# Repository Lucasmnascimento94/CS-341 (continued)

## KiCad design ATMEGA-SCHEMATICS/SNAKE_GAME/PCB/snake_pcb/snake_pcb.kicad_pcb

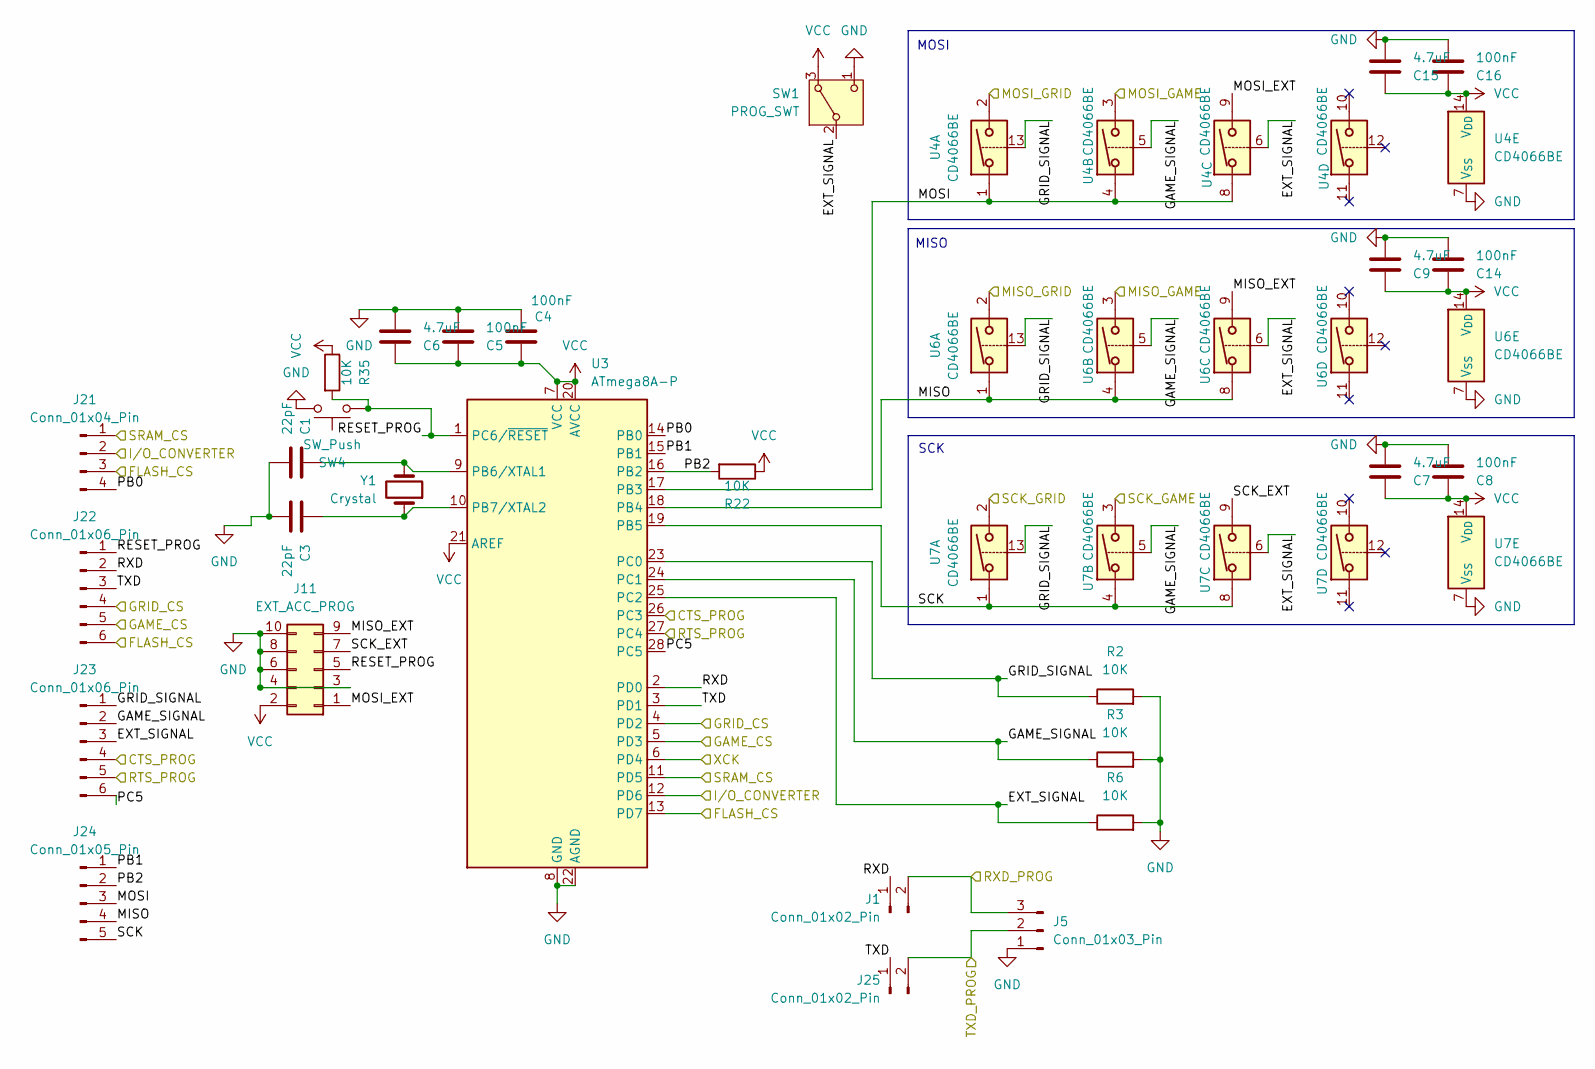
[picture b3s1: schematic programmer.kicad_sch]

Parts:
C1, C3: 22pF; CP_Radial_D5.0mm_P2.50mm
C4, C5, C8, C14, C16: 100nF; C_Disc_D7.5mm_W5.0mm_P5.00mm
C6, C7, C9, C15: 4.7uF; C_Disc_D7.5mm_W5.0mm_P5.00mm
J1: Conn_01x02_Pin; PinSocket_1x02_P2.54mm_Vertical
J5: Conn_01x03_Pin; PinSocket_1x03_P2.54mm_Vertical
J11: EXT_ACC_PROG; IDC-Header_2x05_P2.54mm_Vertical
J21: Conn_01x04_Pin; PinHeader_1x04_P2.54mm_Vertical
J22, J23: Conn_01x06_Pin; PinHeader_1x06_P2.54mm_Vertical
J24: Conn_01x05_Pin; PinHeader_1x05_P2.54mm_Vertical
J25: Conn_01x02_Pin; PinHeader_1x02_P2.54mm_Vertical
R2, R3, R6, R22, R35: 10K; R_Axial_DIN0207_L6.3mm_D2.5mm_P10.16mm_Horizontal
SW1: PROG_SWT; SW_Slide_SPDT_Straight_CK_OS102011MS2Q
SW4: SW_Push; SW_PUSH_1P1T_6x3.5mm_H4.3_APEM_MJTP1243
U3: ATmega8A-P; DIP-28_W7.62mm
U4, U6, U7: CD4066BE; DIP-14_W7.62mm
Y1: Crystal; Resonator-2Pin_W6.0mm_H3.0mm

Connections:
/converter/CTS_CONV: J23.4, U3.26 (PC3); also elsewhere on the board
/converter/RTS_CONV: J23.5, U3.27 (PC4); also elsewhere on the board
/converter/RXD_CONV: J5.2, J25.2; also elsewhere on the board
/converter/TXD_CONV: J1.2, J5.3; also elsewhere on the board
/converter/WAKE_UP: J21.2, U3.12 (PD6); also elsewhere on the board
/game/MISO_GAME: U6.3; also elsewhere on the board
/game/MOSI_GAME: U4.3; also elsewhere on the board
/game/RESET_GAME: J22.5, U3.5 (PD3); also elsewhere on the board
/game/SCK_GAME: U7.3; also elsewhere on the board
/grid/MISO_GRID: U6.2; also elsewhere on the board
/grid/MOSI_GRID: U4.2; also elsewhere on the board
/grid/RESET_GRID: J22.4, U3.4 (PD2); also elsewhere on the board
/grid/SCK_GRID: U7.2; also elsewhere on the board
/grid/SRAM_CS: J21.1, U3.11 (PD5); also elsewhere on the board
/programmer/EXT_SIGNAL: J23.3, R6.1, SW1.2 (B), U3.25 (PC2), U4.6, U6.6, U7.6
/programmer/GAME_SIGNAL: J23.2, R3.1, U3.24 (PC1), U4.5, U6.5, U7.5
/programmer/GRID_SIGNAL: J23.1, R2.1, U3.23 (PC0), U4.13, U6.13, U7.13
/programmer/MISO: J24.4, U3.18 (PB4), U6.1, U6.4, U6.8
/programmer/MISO_EXT: J11.9, U6.9
/programmer/MOSI: J24.3, U3.17 (PB3), U4.1, U4.4, U4.8
/programmer/MOSI_EXT: J11.1, U4.9
/programmer/PB0: J21.4, U3.14 (PB0)
/programmer/PB1: J24.1, U3.15 (PB1)
/programmer/PB2: J24.2, R22.2, U3.16 (PB2)
/programmer/PC5: J23.6, U3.28 (PC5)
/programmer/RESET_PROG: J11.5, J22.1, R35.2, SW4.1, U3.1 (PC6/~RESET)
/programmer/RXD: J1.1, J22.2, U3.2 (PD0)
/programmer/SCK: J24.5, U3.19 (PB5), U7.1, U7.4, U7.8
/programmer/SCK_EXT: J11.7, U7.9
/programmer/TXD: J22.3, J25.1, U3.3 (PD1)
GND: C1.2, C3.2, C4.2, C5.2, C6.2, C7.2, C8.2, C9.2, C14.2, C15.2, C16.2, J5.1, J11.3, J11.4, J11.6, J11.8, J11.10, R2.2, R3.2, R6.2, SW1.1 (C), SW4.2, U3.8 (GND), U3.22 (AGND), U4.7 (V_{SS}), U6.7 (V_{SS}), U7.7 (V_{SS}); also elsewhere on the board
unnamed: C1.1, U3.9 (PB6/XTAL1), Y1.2
unnamed: C3.1, U3.10 (PB7/XTAL2), Y1.1
VCC: C4.1, C5.1, C6.1, C7.1, C8.1, C9.1, C14.1, C15.1, C16.1, J11.2, R22.1, R35.1, SW1.3 (A), U3.7 (VCC), U3.20 (AVCC), U3.21 (AREF), U4.14 (V_{DD}), U6.14 (V_{DD}), U7.14 (V_{DD}); also elsewhere on the board

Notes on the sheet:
SCK
MISO
MOSI

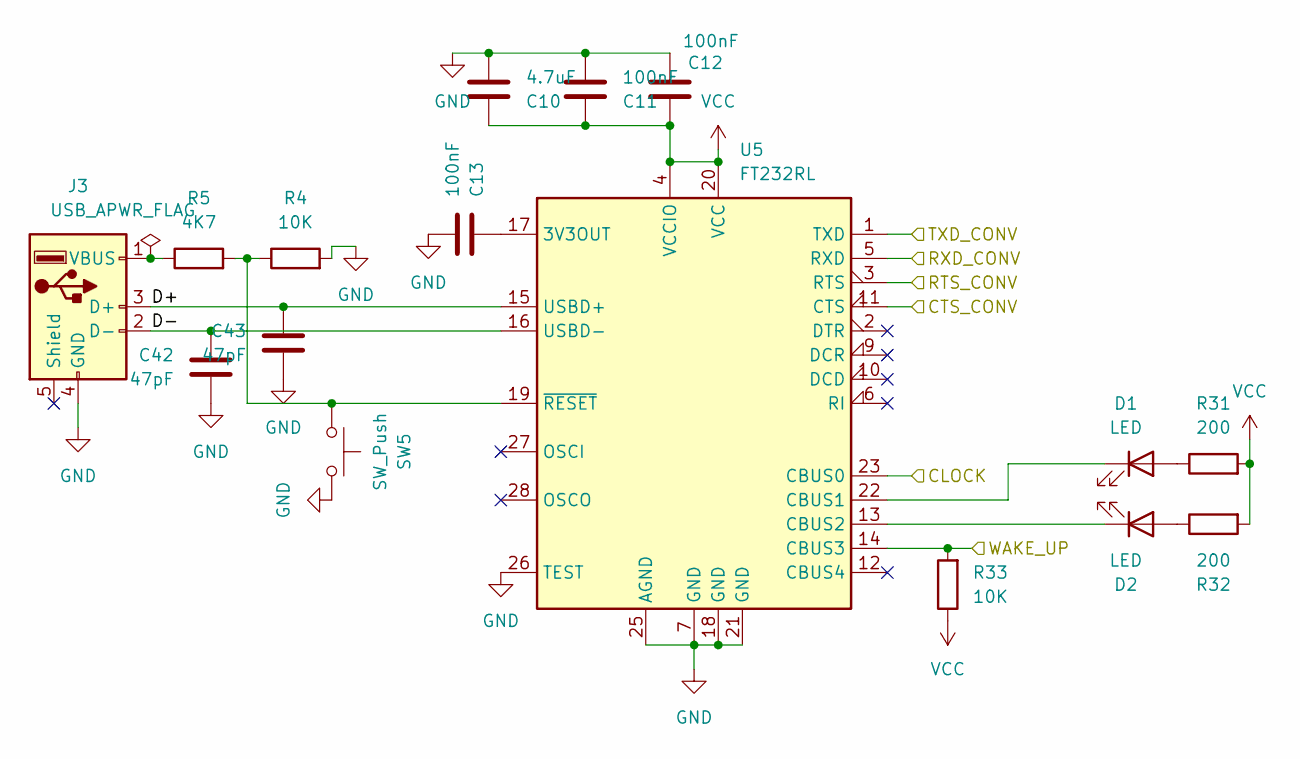
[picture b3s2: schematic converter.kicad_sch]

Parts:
C10: 4.7uF; C_Disc_D7.5mm_W5.0mm_P5.00mm
C11, C12, C13: 100nF; C_Disc_D7.5mm_W5.0mm_P5.00mm
C42, C43: 47pF; C_Disc_D7.5mm_W5.0mm_P5.00mm
D1, D2: LED; LED_D1.8mm_W3.3mm_H2.4mm
J3: USB_A; USB_B_Lumberg_2411_02_Horizontal
R4, R33: 10K; R_Axial_DIN0207_L6.3mm_D2.5mm_P10.16mm_Horizontal
R5: 4K7; R_Axial_DIN0207_L6.3mm_D2.5mm_P10.16mm_Horizontal
R31, R32: 200; R_Axial_DIN0207_L6.3mm_D2.5mm_P10.16mm_Horizontal
SW5: SW_Push; SW_PUSH_1P1T_6x3.5mm_H4.3_APEM_MJTP1243
U5: FT232RL; DIP-28_W15.24mm_LongPads

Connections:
/converter/CTS_CONV: U5.11 (CTS); also elsewhere on the board
/converter/D+: C43.1, J3.3 (D+), U5.15 (USBD+)
/converter/D-: C42.1, J3.2 (D-), U5.16 (USBD-)
/converter/RTS_CONV: U5.3 (RTS); also elsewhere on the board
/converter/RXD_CONV: U5.5 (RXD); also elsewhere on the board
/converter/TXD_CONV: U5.1 (TXD); also elsewhere on the board
/converter/WAKE_UP: R33.2, U5.14 (CBUS3); also elsewhere on the board
GND: C10.2, C11.2, C12.2, C13.2, C42.2, C43.2, J3.4 (GND), R4.2, SW5.2, U5.7 (GND), U5.18 (GND), U5.21 (GND), U5.25 (AGND), U5.26 (TEST); also elsewhere on the board
unnamed: D1.2 (A), R31.1
unnamed: D1.1 (K), U5.22 (CBUS1)
unnamed: D2.2 (A), R32.1
unnamed: D2.1 (K), U5.13 (CBUS2)
unnamed: J3.1 (VBUS), R5.1
unnamed: C13.1, U5.17 (3V3OUT)
unnamed: R4.1, R5.2, SW5.1, U5.19 (~RESET)
VCC: C10.1, C11.1, C12.1, R31.2, R32.2, R33.1, U5.4 (VCCIO), U5.20 (VCC); also elsewhere on the board

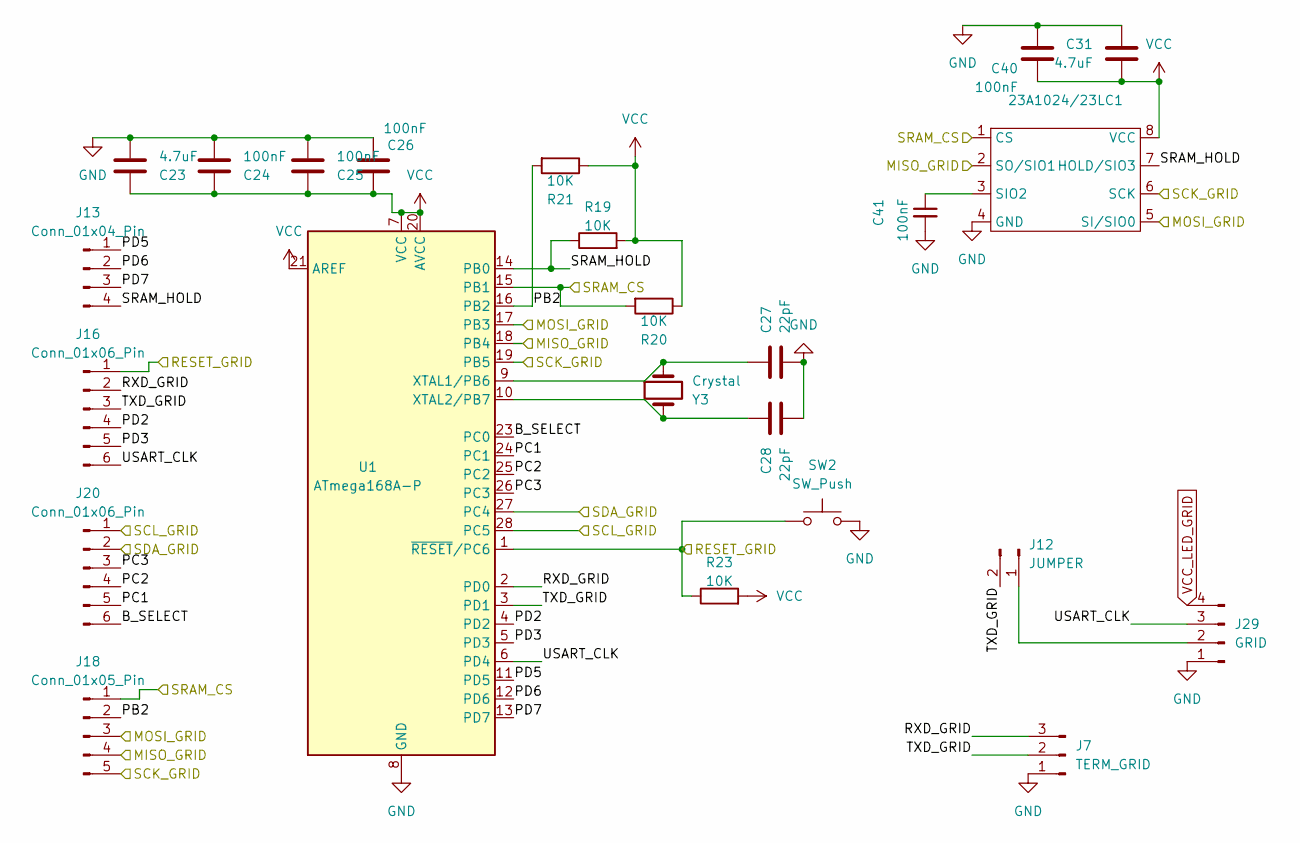
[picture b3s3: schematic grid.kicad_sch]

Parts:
23A1024/23LC1: CERDIP-8_W7.62mm_SideBrazed_Socket
C23, C31: 4.7uF; C_Disc_D7.5mm_W5.0mm_P5.00mm
C24, C25, C26, C40, C41: 100nF; C_Disc_D7.5mm_W5.0mm_P5.00mm
C27, C28: 22pF; CP_Radial_D5.0mm_P2.50mm
J7: TERM_GRID; PinSocket_1x03_P2.54mm_Vertical
J12: JUMPER; PinHeader_1x02_P2.54mm_Vertical
J13: Conn_01x04_Pin; PinHeader_1x04_P2.54mm_Vertical
J16, J20: Conn_01x06_Pin; PinHeader_1x06_P2.54mm_Vertical
J18: Conn_01x05_Pin; PinHeader_1x05_P2.54mm_Vertical
J29: GRID; PinHeader_1x04_P2.54mm_Vertical
R19, R20, R21, R23: 10K; R_Axial_DIN0207_L6.3mm_D2.5mm_P10.16mm_Horizontal
SW2: SW_Push; SW_PUSH_1P1T_6x3.5mm_H4.3_APEM_MJTP1243
U1: ATmega168A-P; DIP-28_W7.62mm
Y3: Crystal; Resonator-2Pin_W6.0mm_H3.0mm

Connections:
/game/SCL_GAME: J20.1, U1.28 (PC5); also elsewhere on the board
/game/SDA_GAME: J20.2, U1.27 (PC4); also elsewhere on the board
/grid/B_SELECT: J20.6, U1.23 (PC0)
/grid/MISO_GRID: 23A1024/23LC1.2 (SO/SIO1), J18.4, U1.18 (PB4); also elsewhere on the board
/grid/MOSI_GRID: 23A1024/23LC1.5 (SI/SIO0), J18.3, U1.17 (PB3); also elsewhere on the board
/grid/PB2: J18.2, R21.2, U1.16 (PB2)
/grid/PC2: J20.4, U1.25 (PC2)
/grid/PC3: J20.3, U1.26 (PC3)
/grid/PD2: J16.4, U1.4 (PD2)
/grid/PD3: J16.5, U1.5 (PD3)
/grid/PD5: J13.1, U1.11 (PD5)
/grid/PD6: J13.2, U1.12 (PD6)
/grid/PD7: J13.3, U1.13 (PD7)
/grid/RESET_GRID: J16.1, R23.1, SW2.1, U1.1 (~RESET/PC6); also elsewhere on the board
/grid/RXD_GRID: J7.3, J16.2, U1.2 (PD0)
/grid/SCK_GRID: 23A1024/23LC1.6 (SCK), J18.5, U1.19 (PB5); also elsewhere on the board
/grid/SRAM_CS: 23A1024/23LC1.1 (CS), J18.1, R20.2, U1.15 (PB1); also elsewhere on the board
/grid/SRAM_HOLD: 23A1024/23LC1.7 (HOLD/SIO3), J13.4, R19.1, U1.14 (PB0)
/grid/TXD_GRID: J7.2, J12.2, J16.3, U1.3 (PD1)
/grid/USART_CLK: J16.6, J29.3, U1.6 (PD4)
GND: 23A1024/23LC1.4 (GND), C23.2, C24.2, C25.2, C26.2, C27.2, C28.2, C31.1, C40.1, C41.2, J7.1, J29.1, SW2.2, U1.8 (GND), U1.22 (GND); also elsewhere on the board
unnamed: 23A1024/23LC1.3 (SIO2), C41.1
unnamed: J12.1, J29.2
unnamed: C27.1, U1.9 (XTAL1/PB6), Y3.1
unnamed: C28.1, U1.10 (XTAL2/PB7), Y3.2
REG_EN_LOW: J20.5, U1.24 (PC1); also elsewhere on the board
VCC: 23A1024/23LC1.8 (VCC), C23.1, C24.1, C25.1, C26.1, C31.2, C40.2, R19.2, R20.1, R21.1, R23.2, U1.7 (VCC), U1.20 (AVCC), U1.21 (AREF); also elsewhere on the board
VCC_LED_GRID: J29.4; also elsewhere on the board

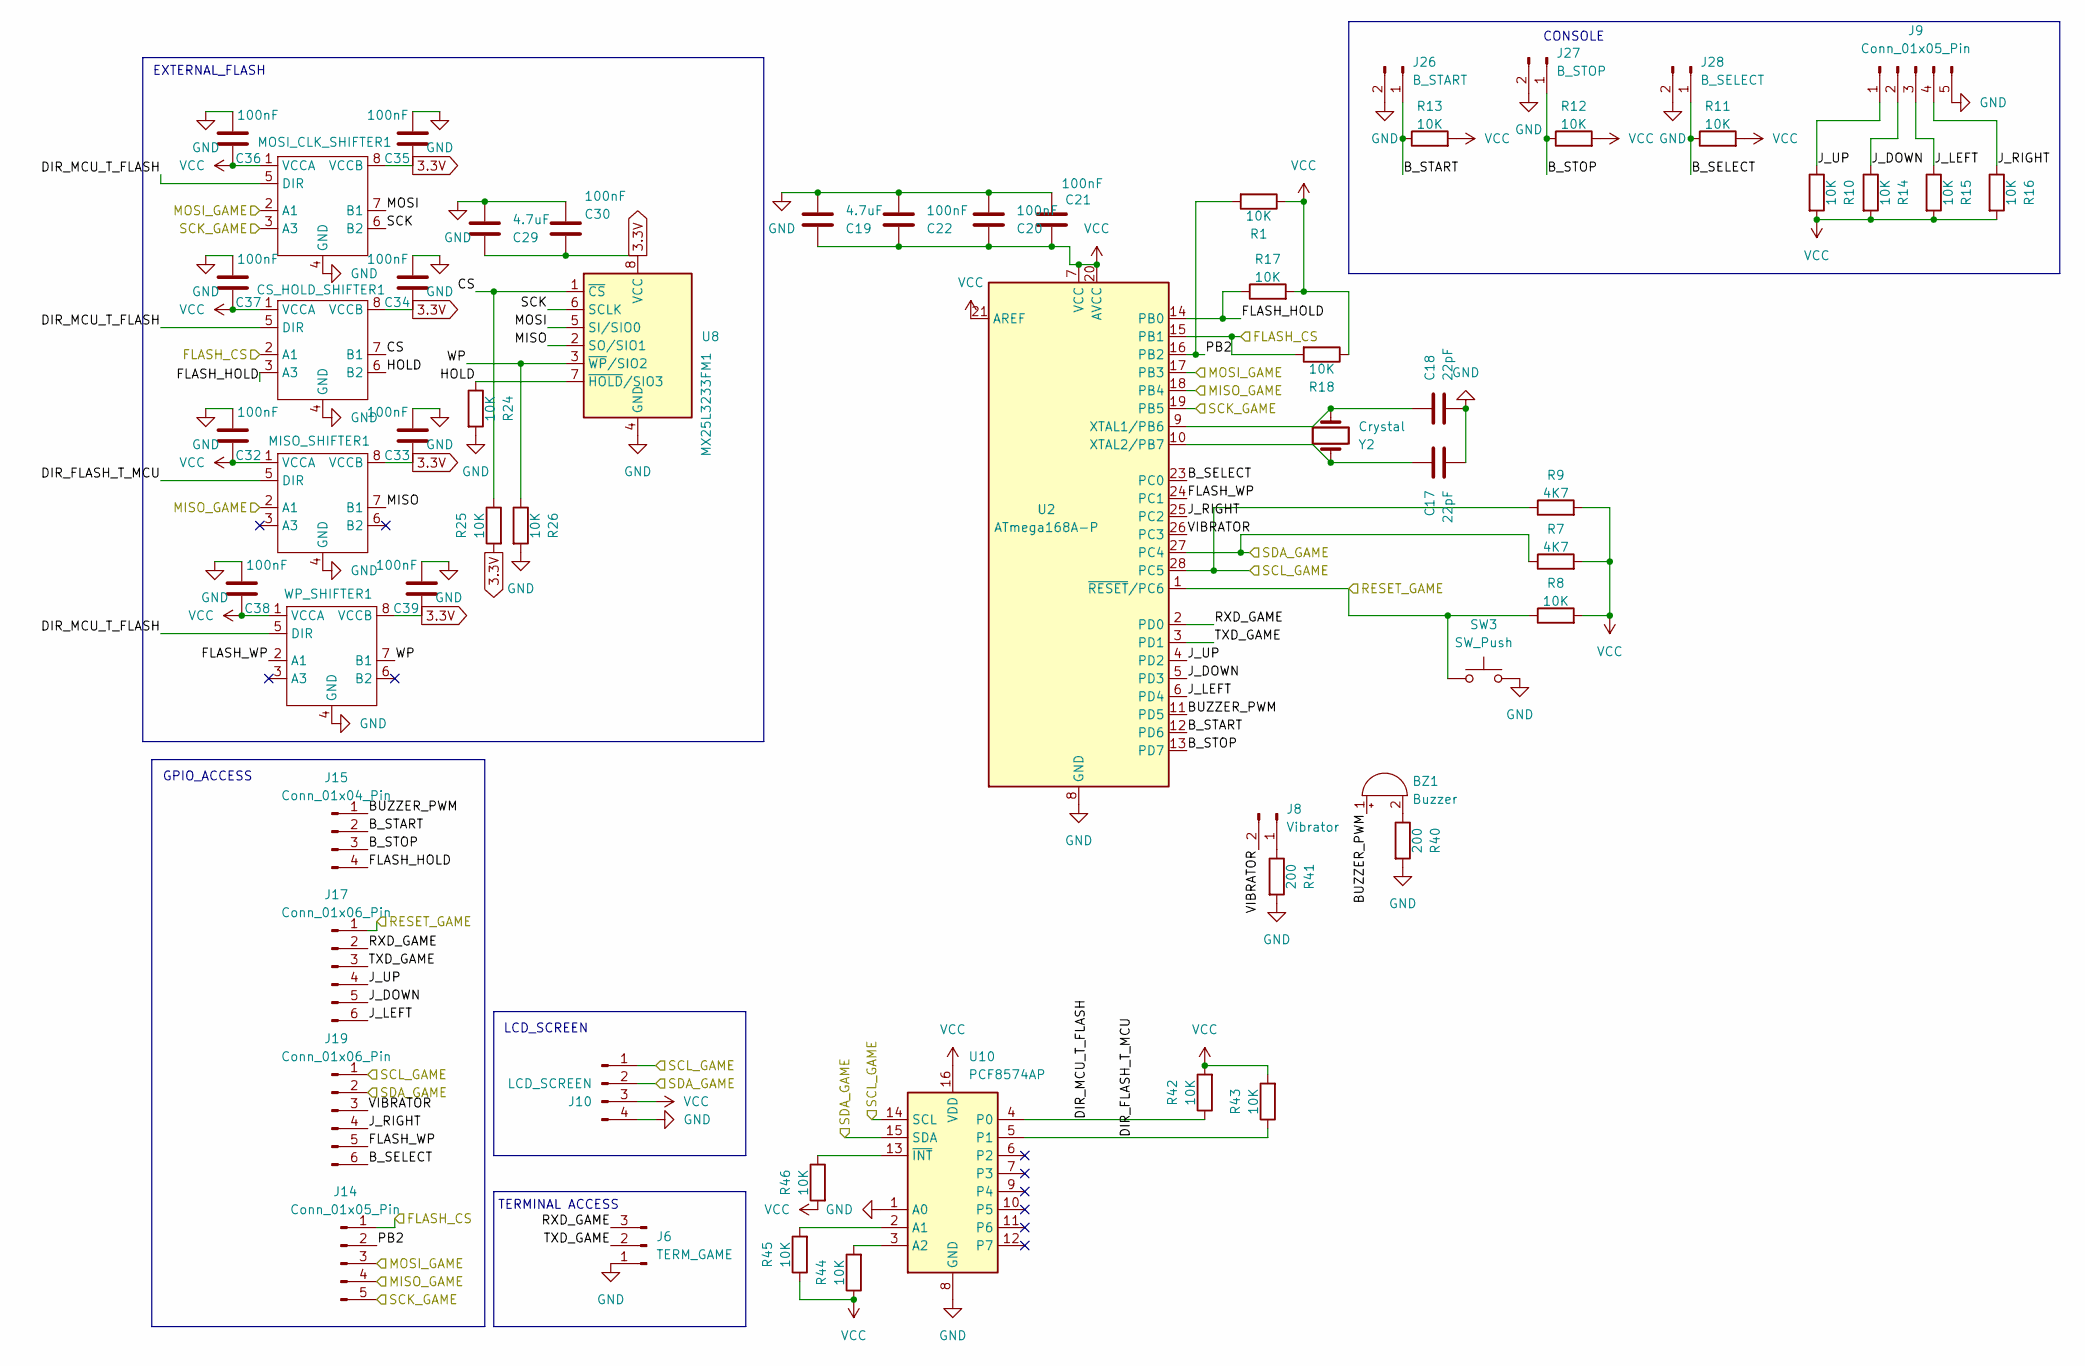
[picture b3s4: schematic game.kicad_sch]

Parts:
BZ1: Buzzer; Buzzer_12x9.5RM7.6
C17, C18: 22pF; CP_Radial_D5.0mm_P2.50mm
C19, C29: 4.7uF; C_Disc_D7.5mm_W5.0mm_P5.00mm
C20, C21, C22, C30, C32, C33, C34, C35, C36, C37, C38, C39: 100nF; C_Disc_D7.5mm_W5.0mm_P5.00mm
CS_HOLD_SHIFTER1: DIP-8_W7.62mm
J6: TERM_GAME; PinSocket_1x03_P2.54mm_Vertical
J8: Vibrator; PinHeader_1x02_P2.54mm_Vertical
J9: Conn_01x05_Pin; PinSocket_1x05_P2.54mm_Vertical
J10: LCD_SCREEN; PinSocket_1x04_P2.54mm_Vertical
J14: Conn_01x05_Pin; PinHeader_1x05_P2.54mm_Vertical
J15: Conn_01x04_Pin; PinHeader_1x04_P2.54mm_Vertical
J17, J19: Conn_01x06_Pin; PinHeader_1x06_P2.54mm_Vertical
J26: B_START; PinHeader_1x02_P2.54mm_Vertical
J27: B_STOP; PinHeader_1x02_P2.54mm_Vertical
J28: B_SELECT; PinHeader_1x02_P2.54mm_Vertical
MISO_SHIFTER1: DIP-8_W7.62mm
MOSI_CLK_SHIFTER1: DIP-8_W7.62mm
R1, R8, R10, R11, R12, R13, R14, R15, R16, R17, R18, R24, R25, R26, R42, R43, R44, R45, R46: 10K; R_Axial_DIN0207_L6.3mm_D2.5mm_P10.16mm_Horizontal
R7, R9: 4K7; R_Axial_DIN0207_L6.3mm_D2.5mm_P10.16mm_Horizontal
R40, R41: 200; R_Axial_DIN0207_L6.3mm_D2.5mm_P10.16mm_Horizontal
SW3: SW_Push; SW_PUSH_1P1T_6x3.5mm_H4.3_APEM_MJTP1243
U2: ATmega168A-P; DIP-28_W7.62mm
U8: MX25L3233FM1; CERDIP-8_W7.62mm_SideBrazed_Socket
U10: PCF8574AP; DIP-16_W7.62mm
WP_SHIFTER1: DIP-8_W7.62mm
Y2: Crystal; Resonator-2Pin_W6.0mm_H3.0mm

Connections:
3.3V: C29.1, C30.1, C33.1, C34.1, C35.1, C39.1, CS_HOLD_SHIFTER1.8 (VCCB), MISO_SHIFTER1.8 (VCCB), MOSI_CLK_SHIFTER1.8 (VCCB), R25.2, U8.8 (VCC), WP_SHIFTER1.8 (VCCB); also elsewhere on the board
/game/BUZZER_PWM: BZ1.1 (+), J15.1, U2.11 (PD5)
/game/B_SELECT: J19.6, J28.1, R11.1, U2.23 (PC0)
/game/B_START: J15.2, J26.1, R13.1, U2.12 (PD6)
/game/B_STOP: J15.3, J27.1, R12.1, U2.13 (PD7)
/game/CS: CS_HOLD_SHIFTER1.7 (B1), R25.1, U8.1 (~CS)
/game/DIR_FLASH_T_MCU: MISO_SHIFTER1.5 (DIR), R43.1, U10.5 (P1)
/game/DIR_MCU_T_FLASH: CS_HOLD_SHIFTER1.5 (DIR), MOSI_CLK_SHIFTER1.5 (DIR), R42.1, U10.4 (P0), WP_SHIFTER1.5 (DIR)
/game/FLASH_HOLD: CS_HOLD_SHIFTER1.3 (A3), J15.4, R17.1, U2.14 (PB0)
/game/FLASH_WP: J19.5, U2.24 (PC1), WP_SHIFTER1.2 (A1)
/game/HOLD: CS_HOLD_SHIFTER1.6 (B2), R24.1, U8.7 (~HOLD/SIO3)
/game/J_DOWN: J9.2, J17.5, R14.1, U2.5 (PD3)
/game/J_LEFT: J9.3, J17.6, R15.1, U2.6 (PD4)
/game/J_RIGHT: J9.4, J19.4, R16.1, U2.25 (PC2)
/game/J_UP: J9.1, J17.4, R10.1, U2.4 (PD2)
/game/MISO: MISO_SHIFTER1.7 (B1), U8.2 (SO/SIO1)
/game/MISO_GAME: J14.4, MISO_SHIFTER1.2 (A1), U2.18 (PB4); also elsewhere on the board
/game/MOSI: MOSI_CLK_SHIFTER1.7 (B1), U8.5 (SI/SIO0)
/game/MOSI_GAME: J14.3, MOSI_CLK_SHIFTER1.2 (A1), U2.17 (PB3); also elsewhere on the board
/game/PB2: J14.2, R1.2, U2.16 (PB2)
/game/RESET_GAME: J17.1, R8.1, SW3.1, U2.1 (~RESET/PC6); also elsewhere on the board
/game/RXD_GAME: J6.3, J17.2, U2.2 (PD0)
/game/SCK: MOSI_CLK_SHIFTER1.6 (B2), U8.6 (SCLK)
/game/SCK_GAME: J14.5, MOSI_CLK_SHIFTER1.3 (A3), U2.19 (PB5); also elsewhere on the board
/game/SCL_GAME: J10.1, J19.1, R9.1, U2.28 (PC5), U10.14 (SCL); also elsewhere on the board
/game/SDA_GAME: J10.2, J19.2, R7.1, U2.27 (PC4), U10.15 (SDA); also elsewhere on the board
/game/TXD_GAME: J6.2, J17.3, U2.3 (PD1)
/game/VIBRATOR: J8.2, J19.3, U2.26 (PC3)
/game/WP: R26.1, U8.3 (~WP/SIO2), WP_SHIFTER1.7 (B1)
GND: C17.2, C18.2, C19.2, C20.2, C21.2, C22.2, C29.2, C30.2, C32.2, C33.2, C34.2, C35.2, C36.2, C37.2, C38.2, C39.2, CS_HOLD_SHIFTER1.4 (GND), J6.1, J9.5, J10.4, J26.2, J27.2, J28.2, MISO_SHIFTER1.4 (GND), MOSI_CLK_SHIFTER1.4 (GND), R24.2, R26.2, R40.2, R41.2, SW3.2, U2.8 (GND), U2.22 (GND), U8.4 (GND), U10.1 (A0), U10.8 (GND), WP_SHIFTER1.4 (GND); also elsewhere on the board
unnamed: BZ1.2 (-), R40.1
unnamed: J8.1, R41.1
unnamed: C18.1, U2.9 (XTAL1/PB6), Y2.1
unnamed: C17.1, U2.10 (XTAL2/PB7), Y2.2
unnamed: R45.2, U10.2 (A1)
unnamed: R44.2, U10.3 (A2)
unnamed: R46.1, U10.13 (~INT)
VCC: C19.1, C20.1, C21.1, C22.1, C32.1, C36.1, C37.1, C38.1, CS_HOLD_SHIFTER1.1 (VCCA), J10.3, MISO_SHIFTER1.1 (VCCA), MOSI_CLK_SHIFTER1.1 (VCCA), R1.1, R7.2, R8.2, R9.2, R10.2, R11.2, R12.2, R13.2, R14.2, R15.2, R16.2, R17.2, R18.1, R42.2, R43.2, R44.1, R45.1, R46.2, U2.7 (VCC), U2.20 (AVCC), U2.21 (AREF), U10.16 (VDD), WP_SHIFTER1.1 (VCCA); also elsewhere on the board

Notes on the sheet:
TERMINAL ACCESS
GPIO_ACCESS
CONSOLE
EXTERNAL_FLASH
LCD_SCREEN

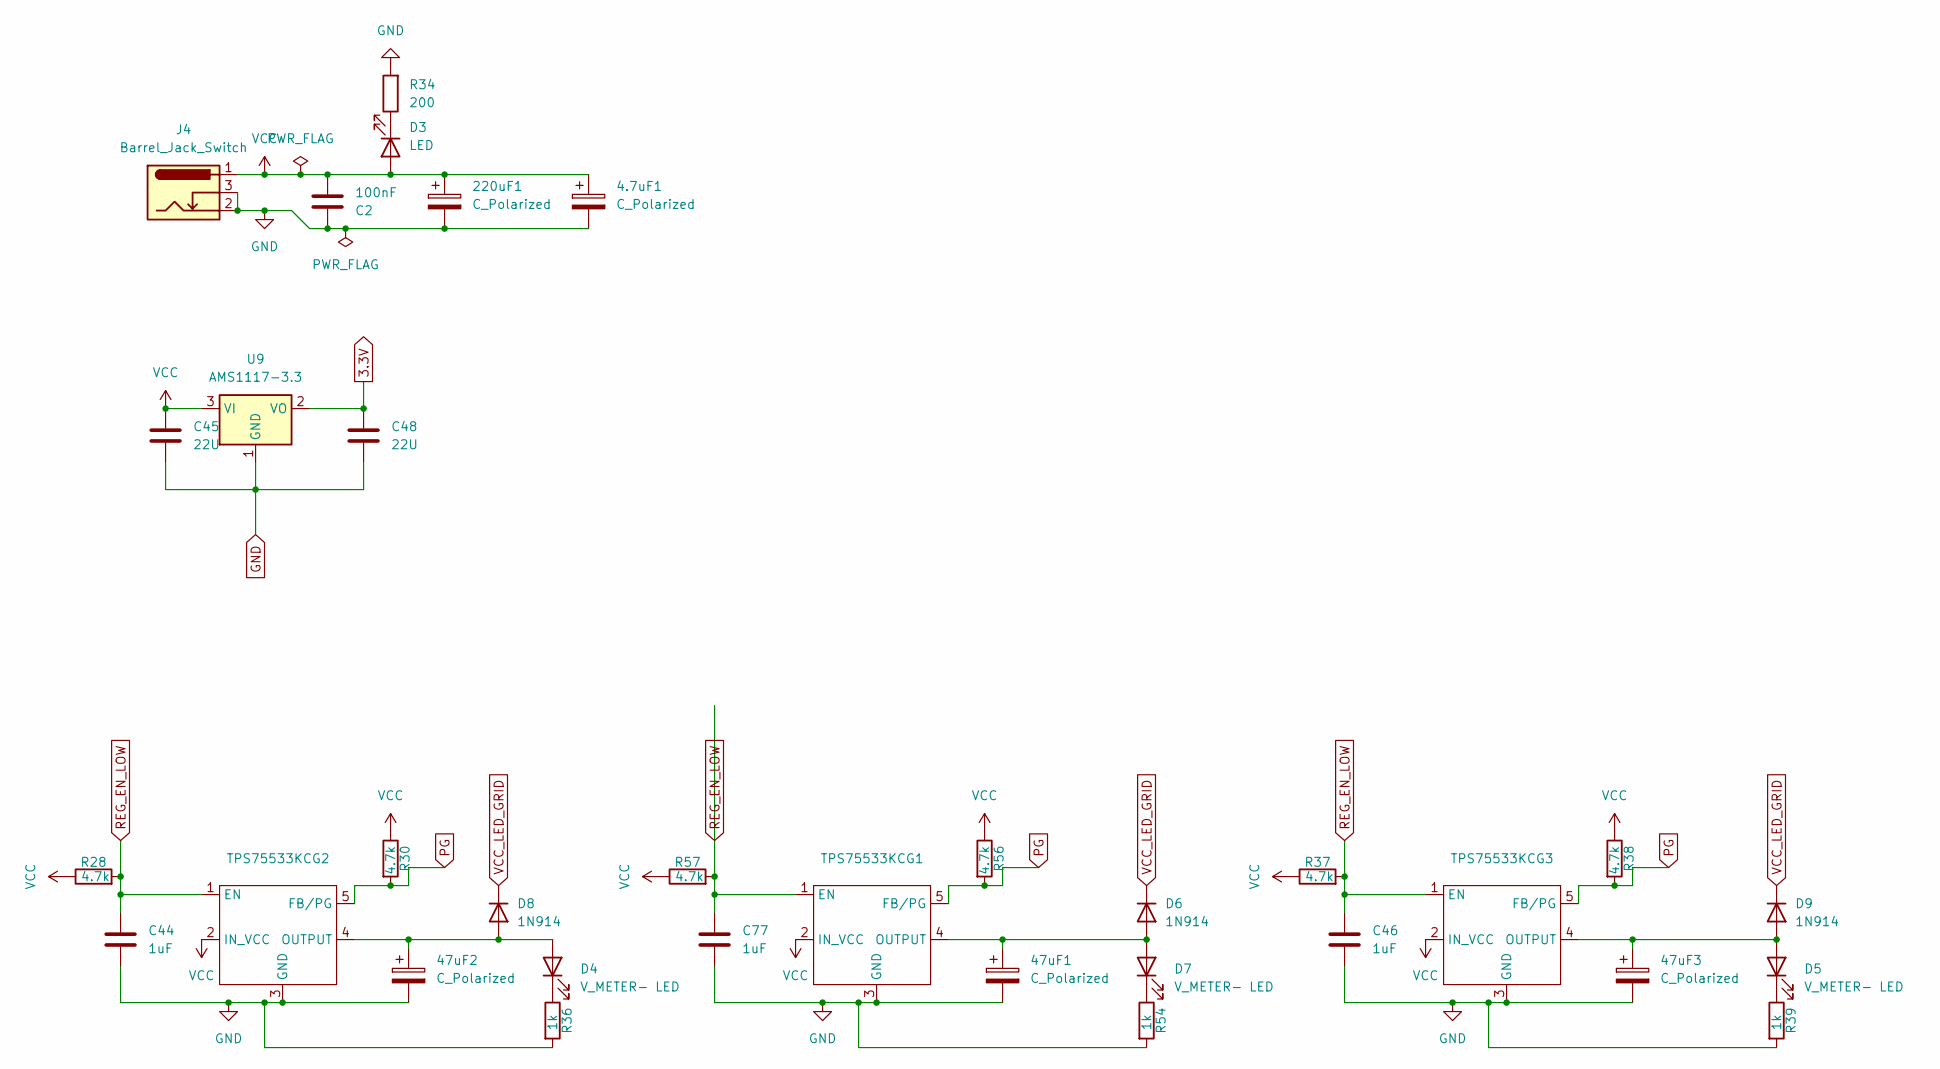
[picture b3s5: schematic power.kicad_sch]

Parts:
4.7uF1, 47uF1, 47uF2, 47uF3, 220uF1: C_Polarized; C_Disc_D3.0mm_W1.6mm_P2.50mm
C2: 100nF; C_Disc_D7.5mm_W5.0mm_P5.00mm
C44, C46, C77: 1uF; C_Disc_D7.5mm_W5.0mm_P5.00mm
C45, C48: 22U; C_Disc_D7.5mm_W5.0mm_P5.00mm
D3: LED; LED_D1.8mm_W3.3mm_H2.4mm
D4, D5, D7: V_METER- LED; LED_D1.8mm_W3.3mm_H2.4mm
D6, D8, D9: 1N914; D_DO-35_SOD27_P7.62mm_Horizontal
J4: Barrel_Jack_Switch; BarrelJack_Horizontal
R28, R30, R37, R38, R56, R57: 4.7k; R_Axial_DIN0207_L6.3mm_D2.5mm_P10.16mm_Horizontal
R34: 200; R_Axial_DIN0207_L6.3mm_D2.5mm_P10.16mm_Horizontal
R36, R39, R54: 1k; R_Axial_DIN0207_L6.3mm_D2.5mm_P10.16mm_Horizontal
TPS75533KCG1, TPS75533KCG2, TPS75533KCG3: TO-220-5_Vertical
U9: AMS1117-3.3; SOT-223-3_TabPin2

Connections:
3.3V: C48.1, U9.2 (VO); also elsewhere on the board
GND: 4.7uF1.2, 47uF1.2, 47uF2.2, 47uF3.2, 220uF1.2, C2.1, C44.2, C45.2, C46.2, C48.2, C77.2, J4.2, J4.3, R34.2, R36.2, R39.2, R54.2, TPS75533KCG1.3 (GND), TPS75533KCG2.3 (GND), TPS75533KCG3.3 (GND), U9.1 (GND); also elsewhere on the board
unnamed: D3.1 (K), R34.1
unnamed: 47uF2.1, D4.2 (A), D8.2 (A), TPS75533KCG2.4 (OUTPUT)
unnamed: D4.1 (K), R36.1
unnamed: 47uF3.1, D5.2 (A), D9.2 (A), TPS75533KCG3.4 (OUTPUT)
unnamed: D5.1 (K), R39.1
unnamed: 47uF1.1, D6.2 (A), D7.2 (A), TPS75533KCG1.4 (OUTPUT)
unnamed: D7.1 (K), R54.1
PG: R30.2, R38.2, R56.2, TPS75533KCG1.5 (FB/PG), TPS75533KCG2.5 (FB/PG), TPS75533KCG3.5 (FB/PG)
REG_EN_LOW: C44.1, C46.1, C77.1, R28.2, R37.2, R57.2, TPS75533KCG1.1 (EN), TPS75533KCG2.1 (EN), TPS75533KCG3.1 (EN); also elsewhere on the board
VCC: 4.7uF1.1, 220uF1.1, C2.2, C45.1, D3.2 (A), J4.1, R28.1, R30.1, R37.1, R38.1, R56.1, R57.1, TPS75533KCG1.2 (IN_VCC), TPS75533KCG2.2 (IN_VCC), TPS75533KCG3.2 (IN_VCC), U9.3 (VI); also elsewhere on the board
VCC_LED_GRID: D6.1 (K), D8.1 (K), D9.1 (K); also elsewhere on the board

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
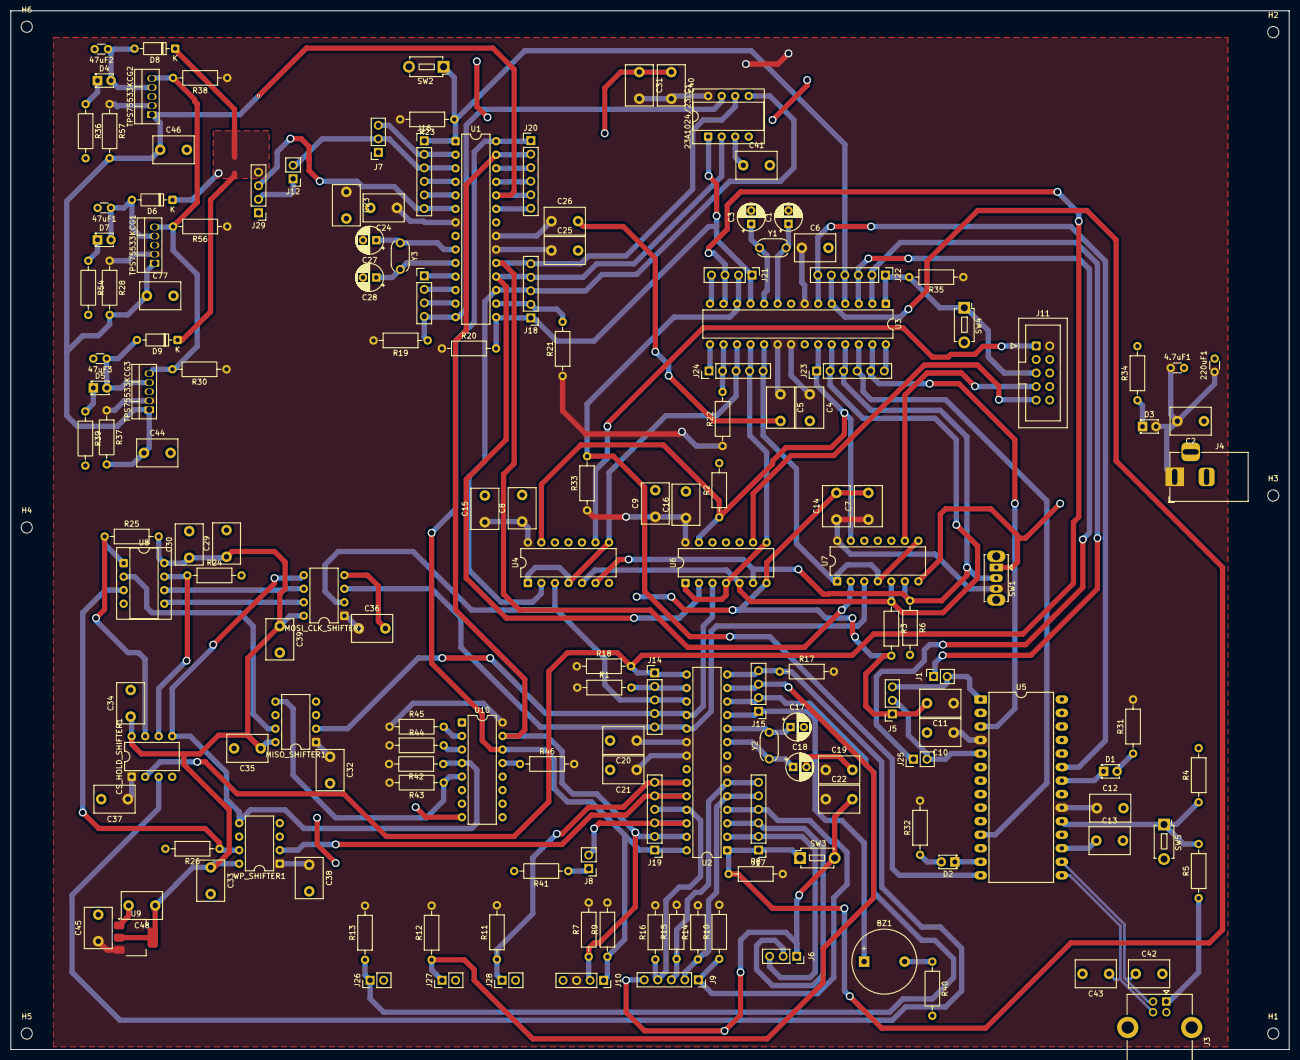
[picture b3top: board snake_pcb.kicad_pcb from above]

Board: 2 copper layers, 240.0 x 195.0 mm, 170 parts (0 on the bottom side), 104 nets.

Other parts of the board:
H1, H2, H3, H4, H5, H6: MountingHole; MountingHole_2.1mm

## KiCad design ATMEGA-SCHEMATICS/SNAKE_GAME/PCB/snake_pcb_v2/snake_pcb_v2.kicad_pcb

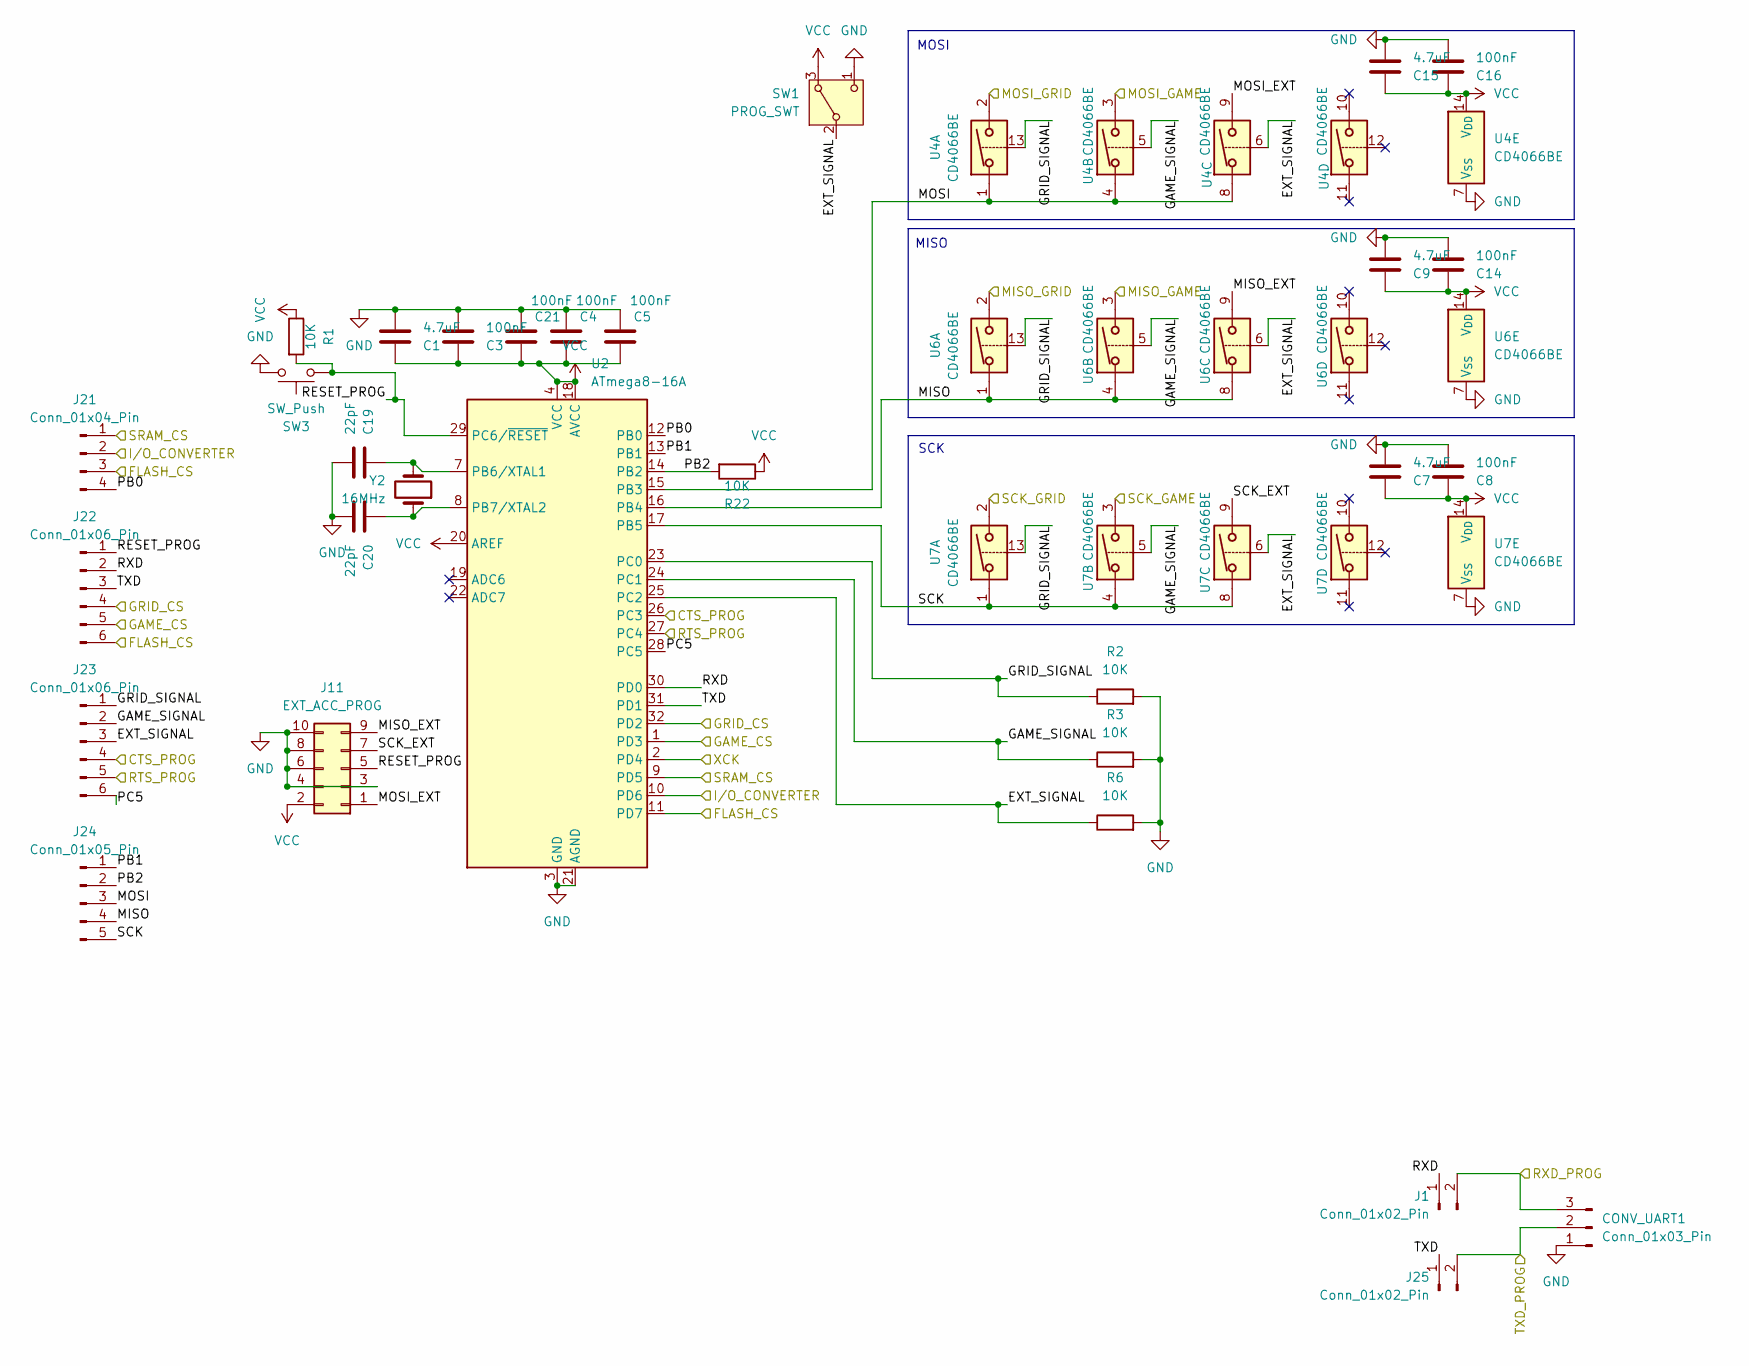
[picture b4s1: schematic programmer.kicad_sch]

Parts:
C1, C7, C9, C15: 4.7uF; C_0805_2012Metric
C3, C4, C5, C8, C14, C16, C21: 100nF; C_0402_1005Metric
C19, C20: 22pF; C_0402_1005Metric
CONV_UART1: Conn_01x03_Pin; PinSocket_1x03_P2.54mm_Vertical
J1: Conn_01x02_Pin; PinSocket_1x02_P2.54mm_Vertical
J11: EXT_ACC_PROG; IDC-Header_2x05_P2.54mm_Vertical
J21: Conn_01x04_Pin; PinHeader_1x04_P2.54mm_Vertical
J22, J23: Conn_01x06_Pin; PinHeader_1x06_P2.54mm_Vertical
J24: Conn_01x05_Pin; PinHeader_1x05_P2.54mm_Vertical
J25: Conn_01x02_Pin; PinHeader_1x02_P2.54mm_Vertical
R1, R2, R3, R6, R22: 10K; R_0402_1005Metric
SW1: PROG_SWT; SW_Slide_SPDT_Straight_CK_OS102011MS2Q
SW3: SW_Push; SW_PUSH_1P1T_6x3.5mm_H4.3_APEM_MJTP1243
U2: ATmega8-16A; TQFP-32_7x7mm_P0.8mm
U4, U6, U7: CD4066BE; DIP-14_W7.62mm
Y2: 16MHz; Crystal_SMD_3225-4Pin_3.2x2.5mm_HandSoldering

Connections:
/converter/CLOCK: U2.2 (PD4); also elsewhere on the board
/converter/CTS_CONV: J23.4, U2.26 (PC3); also elsewhere on the board
/converter/RTS_CONV: J23.5, U2.27 (PC4); also elsewhere on the board
/converter/RXD_CONV: CONV_UART1.2, J25.2; also elsewhere on the board
/converter/TXD_CONV: CONV_UART1.3, J1.2; also elsewhere on the board
/converter/WAKE_UP: J21.2, U2.10 (PD6); also elsewhere on the board
/game/FLASH_CS: J21.3, J22.6, U2.11 (PD7); also elsewhere on the board
/game/MISO_GAME: U6.3; also elsewhere on the board
/game/MOSI_GAME: U4.3; also elsewhere on the board
/game/RESET_GAME: J22.5, U2.1 (PD3); also elsewhere on the board
/game/SCK_GAME: U7.3; also elsewhere on the board
/grid/MISO_GRID: U6.2; also elsewhere on the board
/grid/MOSI_GRID: U4.2; also elsewhere on the board
/grid/RESET_GRID: J22.4, U2.32 (PD2); also elsewhere on the board
/grid/SCK_GRID: U7.2; also elsewhere on the board
/grid/SRAM_CS: J21.1, U2.9 (PD5); also elsewhere on the board
/programmer/EXT_SIGNAL: J23.3, R6.1, SW1.2 (B), U2.25 (PC2), U4.6, U6.6, U7.6
/programmer/GAME_SIGNAL: J23.2, R3.1, U2.24 (PC1), U4.5, U6.5, U7.5
/programmer/GRID_SIGNAL: J23.1, R2.1, U2.23 (PC0), U4.13, U6.13, U7.13
/programmer/MISO: J24.4, U2.16 (PB4), U6.1, U6.4, U6.8
/programmer/MISO_EXT: J11.9, U6.9
/programmer/MOSI: J24.3, U2.15 (PB3), U4.1, U4.4, U4.8
/programmer/MOSI_EXT: J11.1, U4.9
/programmer/PB0: J21.4, U2.12 (PB0)
/programmer/PB1: J24.1, U2.13 (PB1)
/programmer/PB2: J24.2, R22.2, U2.14 (PB2)
/programmer/PC5: J23.6, U2.28 (PC5)
/programmer/RESET_PROG: J11.5, J22.1, R1.2, SW3.1, U2.29 (PC6/~RESET)
/programmer/RXD: J1.1, J22.2, U2.30 (PD0)
/programmer/SCK: J24.5, U2.17 (PB5), U7.1, U7.4, U7.8
/programmer/SCK_EXT: J11.7, U7.9
/programmer/TXD: J22.3, J25.1, U2.31 (PD1)
GND: C1.2, C3.2, C4.2, C5.2, C7.2, C8.2, C9.2, C14.2, C15.2, C16.2, C19.2, C20.2, C21.2, CONV_UART1.1, J11.3, J11.4, J11.6, J11.8, J11.10, R2.2, R3.2, R6.2, SW1.1 (C), SW3.2, U2.3 (GND), U2.5 (GND), U2.21 (AGND), U4.7 (V_{SS}), U6.7 (V_{SS}), U7.7 (V_{SS}); also elsewhere on the board
unnamed: C19.1, U2.7 (PB6/XTAL1), Y2.2
unnamed: C20.1, U2.8 (PB7/XTAL2), Y2.1
VCC: C1.1, C3.1, C4.1, C5.1, C7.1, C8.1, C9.1, C14.1, C15.1, C16.1, C21.1, J11.2, R1.1, R22.1, SW1.3 (A), U2.4 (VCC), U2.6 (VCC), U2.18 (AVCC), U2.20 (AREF), U4.14 (V_{DD}), U6.14 (V_{DD}), U7.14 (V_{DD}); also elsewhere on the board

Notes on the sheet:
SCK
MISO
MOSI
